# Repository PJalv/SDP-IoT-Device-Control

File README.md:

<p align="center">
    <h1 align="center">IoT Device Control System</h1>
</p>
<div align="center">
    <em>Spring 2024 Senior Design Project </em>
</div>
<p align="center">
    <em> Dylan St Laurent & Jorge Suarez </em>
</p>

<p align="center">

<p>
<p align="center">
	<!-- default option, no dependency badges. -->
</p>

<br><!-- TABLE OF CONTENTS -->

<details>
  <summary>Table of Contents</summary><br>

- [Overview](#overview)
- [Features](#features)
- [Repository Structure](#repository-structure)
- [Modules](#modules)
- [Getting Started](#getting-started)
  - [Installation](#installation)
  - [Usage](#usage)
- [Project Roadmap](#project-roadmap)
- [License](#license)
- [Acknowledgments](#acknowledgments)
</details>
<hr>

## Overview

This Senior project is structured to leverage a combination of hardware components and software technologies to provide a comprehensive IoT device control system. Here's an overview of the project's structure and the technologies used:

### Components:
1. **ESP32 Microcontrollers**: These are responsible for device control, data collection, and communication.
2. **Raspberry Pi**: Serves as a local server or gateway, facilitating the interface between ESP32 devices and the cloud server.
3. **Cloud Server**: Manages backend services, databases, and ensures data synchronization and remote access.
4. **Mobile App**: Enables users to interact with the IoT system, control devices, and view data.

### Software Technologies:
- **ESP-IDF**: This is used for programming ESP32 devices, providing essential IoT tools and libraries.
- **FreeRTOS**: Provides a real-time operating system for ESP32 devices, ensuring efficient resource management and task scheduling. We leverage FreeRTOS to separate vital ESP functions like WiFi and MQTT, allowing each to operate independently and efficiently.
- **MQTT Protocol**: Provides efficient real-time messaging across devices and servers.
- **Bun.js**: Implemented on the Raspberry Pi for fast package management and development.
- **React Native**: Utilized for developing the cross-platform mobile application.
- **WebSocket**: Supports real-time data transmission to the mobile app.
- **Go (Golang)**: Specifically used on the cloud server for its robust support for concurrency. Go routines and channels are employed to manage multiple device data streams simultaneously, significantly enhancing the system's scalability and its ability to handle large volumes of IoT device communications efficiently.

---

## Features

|     | Feature           | Description                                                                                                                                                                                         |
| --- | ----------------- | --------------------------------------------------------------------------------------------------------------------------------------------------------------------------------------------------- |
| ⚙️  | **Architecture**  | _Utilizes a modular architecture with technologies such as Go, React Native, and Expo, orchestrated by CMake for IoT device control._ |
| 🔌  | **Integrations**  | _Incorporates JWT for security, MQTT for device messaging, and WebSocket for real-time communication, supporting web and mobile functionalities._ |
| 🧩  | **Modularity**    | _Features distinct components like fan_device and main, which enhance reusability and maintainability._ |
| 🛡️  | **Security**      | _Employs JWT and secure communication protocols such as MQTT and WebSocket to ensure data protection and secure access._ |
| 🚀  | **Scalability**   | _Supports increased traffic and load efficiently through its modular architecture and scalable technologies._ |

---

## Repository Structure

```sh
└── SDP-IoT-Device-Control/
    ├── README.md
    ├── schematics
    │   ├── AudioDriver
    │   ├── Espressif
    │   ├── FanSystem
    │   ├── LED_Device
    │   └── Power
    └── source_code
        ├── IOT-App
        ├── cloud_websocket
        ├── dashboard_gui
        ├── fan_device
        ├── led_device
        └── utils
```

---

## Modules

<details closed><summary>Fan Device Main Module</summary>

| File                                                                                                                           | Summary                                                                                                                                                                                                                                                                        |
| ------------------------------------------------------------------------------------------------------------------------------ | ------------------------------------------------------------------------------------------------------------------------------------------------------------------------------------------------------------------------------------------------------------------------------ |
| [audio.h](https://github.com/PJalv/SDP-IoT-Device-Control/blob/master/source_code/fan_device/main/audio.h)                     | Enables setting up I2S audio with a defined buffer size for the fan device in the SDP-IoT-Device-Control repository.                                                                                                                                                           |
| [init.h](https://github.com/PJalv/SDP-IoT-Device-Control/blob/master/source_code/fan_device/main/init.h)                       | Initializes and finalizes the setup for the IoT fan device. Manages the initialization of FreeRTOS and GPIO, essential for device control. Part of the IoT Device Control repository structure under fan_device.                                                               |
| [main.c](https://github.com/PJalv/SDP-IoT-Device-Control/blob/master/source_code/fan_device/main/main.c)                       | Initializes system, sets up WiFi and MQTT tasks, processes events, maintains heartbeat, and handles counts. Coordinates device functionality within the SDP-IoT-Device-Control repositorys architecture.                                                                       |
| [tasks.h](https://github.com/PJalv/SDP-IoT-Device-Control/blob/master/source_code/fan_device/main/tasks.h)                     | Publishing status, playing audio, controlling breeze mode, managing tasks, establishing Wi-Fi connection, handling MQTT communication, managing heartbeats, and processing events. Crucial for fan system operation within the IoT device control architecture.                |
| [storage_nvs.h](https://github.com/PJalv/SDP-IoT-Device-Control/blob/master/source_code/fan_device/main/storage_nvs.h)         | Manages fan configuration data using Non-Volatile Storage (NVS) for the fan device within the SDP-IoT-Device-Control repositorys architecture. Key functionalities include setting and retrieving fan power, function, and duty cycle information.                             |
| [fan.h](https://github.com/PJalv/SDP-IoT-Device-Control/blob/master/source_code/fan_device/main/fan.h)                         | Implements fan control functionalities and interfaces with LED driver for RPM and power button handling. Manages duty cycle adjustments and interrupts, integrating with MQTT data for IoT device communication within the parent repositorys IoT device control architecture. |

</details>

<details closed><summary>Cloud WebSocket Broker (JavaScript)</summary>

| File                                                                                                                                     | Summary                                                                                                                                                                                                                                                                                                                                                                     |
| ---------------------------------------------------------------------------------------------------------------------------------------- | --------------------------------------------------------------------------------------------------------------------------------------------------------------------------------------------------------------------------------------------------------------------------------------------------------------------------------------------------------------------------- |
| [broker.js](https://github.com/PJalv/SDP-IoT-Device-Control/blob/master/source_code/cloud_websocket/broker-js/broker.js)                 | Establishes connectivity between MQTT broker and WebSocket server, facilitating real-time data exchange. Handles JWT token generation and verification, synchronizing data with the broker. Manages reconnections and error handling, enhancing reliability for IoT device control system.                                                                                  |

</details>

<details closed><summary>Cloud WebSocket Server (Go)</summary>

| File                                                                                                                     | Summary                                                                                                                                                                                                                                                                                               |
| ------------------------------------------------------------------------------------------------------------------------ | ----------------------------------------------------------------------------------------------------------------------------------------------------------------------------------------------------------------------------------------------------------------------------------------------------- |
| [server.go](https://github.com/PJalv/SDP-IoT-Device-Control/blob/master/source_code/cloud_websocket/server-go/server.go) | Orchestrates WebSocket communication for IoT devices. Manages client connections, token verification, and message distribution in a secure manner. Handles commands and responses, gracefully falling back on failure. Monitors domain status and switches services dynamically for robust operation. |

</details>

<details closed><summary>LED Device Managed Components (Espressif LED Strip)</summary>

| File                                                                                                                                                                      | Summary                                                                                                                                                                                                                                                    |
| ------------------------------------------------------------------------------------------------------------------------------------------------------------------------- | ---------------------------------------------------------------------------------------------------------------------------------------------------------------------------------------------------------------------------------------------------------- |
| [led_strip_spi.h](https://github.com/PJalv/SDP-IoT-Device-Control/blob/master/source_code/led_device/managed_components/espressif__led_strip/include/led_strip_spi.h)     | Implements creation of LED strip on SPI MOSI channel. Manages LED strip configuration and SPI specific settings to create LED strip handle successfully, handling errors like invalid arguments or unsupported configurations.                             |
| [led_strip.h](https://github.com/PJalv/SDP-IoT-Device-Control/blob/master/source_code/led_device/managed_components/espressif__led_strip/include/led_strip.h)             | Defines functions to manage RGB, RGBW, and HSV colors for LED strips. Contains methods to set colors for individual pixels, refresh LED memory, clear LED strip, and free resources. Enables control and customization of LED strip colors in IoT devices. |

</details>

<details closed><summary>LED Device Main Module</summary>

| File                                                                                                                           | Summary                                                                                                                                                                                                                                                                                                                                                                                                                                                                                                                                                                                                                                                                                                                                                                                                                              |
| ------------------------------------------------------------------------------------------------------------------------------ | ------------------------------------------------------------------------------------------------------------------------------------------------------------------------------------------------------------------------------------------------------------------------------------------------------------------------------------------------------------------------------------------------------------------------------------------------------------------------------------------------------------------------------------------------------------------------------------------------------------------------------------------------------------------------------------------------------------------------------------------------------------------------------------------------------------------------------------ |
| [led_config.c](https://github.com/PJalv/SDP-IoT-Device-Control/blob/master/source_code/led_device/main/led_config.c)           | Creates LED configuration for LED device with specified GPIO, LED count, and pixel format. Initializes LED strip object using SPI backend for improved performance, leveraging DMA support.                                                                                                                                                                                                                                                                                                                                                                                                                                                                                                                                                                                                                                          |
| [main.c](https://github.com/PJalv/SDP-IoT-Device-Control/blob/master/source_code/led_device/main/main.c)                       | The `main.c` file in the `led_device` module of the `SDP-IoT-Device-Control` repository serves as the main entry point for controlling LED devices. It integrates with various system components like I2S drivers, FreeRTOS tasks, LED strip libraries, MQTT protocols for communication, and Wi-Fi configurations. The code handles LED configurations, GPIO interactions, and JSON parsing to facilitate LED device functionality. Through this file, the LED device module manages LED operations, synchronization, and communication with the broader IoT infrastructure.This code supports the overarching architecture of the repository by providing a crucial component for controlling LED devices within the IoT ecosystem, ensuring seamless integration and communication with other system modules and functionalities. |
| [storage_nvs.h](https://github.com/PJalv/SDP-IoT-Device-Control/blob/master/source_code/led_device/main/storage_nvs.h)         | Manages LED device configuration data using Non-Volatile Storage in the repositorys LED device module, enhancing persistence and reliability.                                                                                                                                                                                                                                                                                                                                                                                                                                                                                                                                                                                                                                                                                        |

</details>

<details closed><summary>Dashboard GUI</summary>

| File                                                                                                                       | Summary                                                                                                                                                                                                                                                              |
| -------------------------------------------------------------------------------------------------------------------------- | -------------------------------------------------------------------------------------------------------------------------------------------------------------------------------------------------------------------------------------------------------------------- |
| [gui.py](https://github.com/PJalv/SDP-IoT-Device-Control/blob/master/source_code/dashboard_gui/gui.py)                     | Facilitates interaction with MQTT broker through Eel GUI for IoT device control. Dynamically updates broker settings, reads JSON storage, and publishes messages. Handles MQTT connection and displays connection status in the GUI, enhancing user experience.      |
| [store.py](https://github.com/PJalv/SDP-IoT-Device-Control/blob/master/source_code/dashboard_gui/store.py)                 | Manages MQTT connections, updates device statuses, and detects disconnected devices. Subscribes to specific topics, parses messages, and updates JSON storage. Handles message receiving and device disconnection checks for LED and fan devices in the IoT system.  |
| [storage.json](https://github.com/PJalv/SDP-IoT-Device-Control/blob/master/source_code/dashboard_gui/storage.json)         | Stores device status, power, and configurations for fan and LED devices-Facilitates real-time monitoring and control of devices via the dashboard GUI within the IoT system                                                                                          |

</details>

<details closed><summary>Dashboard GUI Web (JavaScript)</summary>

| File                                                                                                                    | Summary                                                                                                                                                                                                                                                                |
| ----------------------------------------------------------------------------------------------------------------------- | ---------------------------------------------------------------------------------------------------------------------------------------------------------------------------------------------------------------------------------------------------------------------- |
| [settings.js](https://github.com/PJalv/SDP-IoT-Device-Control/blob/master/source_code/dashboard_gui/web/JS/settings.js) | Retrieves, displays, and updates broker settings and status for IoT device control. Integrates with backend APIs and UI elements. Facilitates MQTT connection handling and status monitoring, ensuring seamless communication with devices.                            |
| [led.js](https://github.com/PJalv/SDP-IoT-Device-Control/blob/master/source_code/dashboard_gui/web/JS/led.js)           | Improves LED control interface. Dynamically updates LED settings and colors based on user inputs. Facilitates toggling power and selecting operation modes using MQTT messaging. Enhances user experience by enabling real-time interaction with LED device.           |
| [app.js](https://github.com/PJalv/SDP-IoT-Device-Control/blob/master/source_code/dashboard_gui/web/JS/app.js)           | Implements MQTT connection and data update logic for IoT devices integration. Manages device statuses and controls via a dashboard interface. Visualizes device status and allows dynamic device control. Dynamically updates interface elements based on device data. |
| [fan.js](https://github.com/PJalv/SDP-IoT-Device-Control/blob/master/source_code/dashboard_gui/web/JS/fan.js)           | Manages fan speed control, power toggling, and data updates using MQTT messages. Dynamically displays fan status, RPM, and mode in a responsive GUI. Enables fan mode selection and updates fan parameters through MQTT communication.                                 |

</details>

<details closed><summary>Dashboard GUI Web (HTML)</summary>

| File                                                                                                                                | Summary                                                                                                                                                                                                                                                                                                                |
| ----------------------------------------------------------------------------------------------------------------------------------- | ---------------------------------------------------------------------------------------------------------------------------------------------------------------------------------------------------------------------------------------------------------------------------------------------------------------------- |
| [index.html](https://github.com/PJalv/SDP-IoT-Device-Control/blob/master/source_code/dashboard_gui/web/html/index.html)             | Generates a responsive dashboard GUI with cards for fan and LED devices. Allows toggling power and settings, displaying device status dynamically. Incorporates Bootstrap CSS and icons for a user-friendly interface.                                                                                                 |
| [Settings.html](https://github.com/PJalv/SDP-IoT-Device-Control/blob/master/source_code/dashboard_gui/web/html/Settings.html)       | Creates a responsive settings interface for configuring the IoT devices broker connection. Features include input fields for broker name, IP address, and port number, with a Connect' button. Leverages Bootstrap for styling and jQuery for functionality.                                                           |
| [eel.js](https://github.com/PJalv/SDP-IoT-Device-Control/blob/master/source_code/dashboard_gui/web/html/eel.js)                     | Enables dynamic communication between Python and JavaScript, facilitating function exposure and asynchronous calls. Handles WebSocket interactions with an embedded Python app, supporting customization of window size and position for a web-based dashboard GUI.                                                    |
| [FanSettings.html](https://github.com/PJalv/SDP-IoT-Device-Control/blob/master/source_code/dashboard_gui/web/html/FanSettings.html) | Showcases an interactive web interface for managing fan settings. Offers power toggling, speed adjustment, breeze mode selection, and real-time statistical data display. Enhances user experience with Bootstrap styling and jQuery functionalities. Integrated for seamless device control in the SDP-IoT ecosystem. |
| [LEDSettings.html](https://github.com/PJalv/SDP-IoT-Device-Control/blob/master/source_code/dashboard_gui/web/html/LEDSettings.html) | Defines the interactive LED device settings interface in the dashboard. Displays color and function options, power toggle, and current stats visualization. Utilizes Bootstrap templates and jQuery for dynamic behavior, enhancing user control over the LED device.                                                  |

</details>

<details closed><summary>Utility Modules</summary>

| File                                                                                           | Summary                                                                                                                                                                                                                                                                       |
| ---------------------------------------------------------------------------------------------- | ----------------------------------------------------------------------------------------------------------------------------------------------------------------------------------------------------------------------------------------------------------------------------- |
| [wifi.h](https://github.com/PJalv/SDP-IoT-Device-Control/blob/master/source_code/utils/wifi.h) | Enables WiFi connectivity for IoT devices. Declares WiFi connection variables and functions. Facilitates seamless integration with parent repositorys cloud and device modules.                                                                                               |
| [mqtt.h](https://github.com/PJalv/SDP-IoT-Device-Control/blob/master/source_code/utils/mqtt.h) | Defines MQTT functionality for IoT devices, supporting integer and JSON payloads. Manages data with semaphores and tasks, handling message events through subscriptions and publications. Facilitates efficient communication within the SDP-IoT-Device-Control architecture. |

</details>

<details closed><summary>IoT App</summary>

| File                                                                                                                   | Summary                                                                                                                                                                                                                                                                                                                                                                                                                                                                                                                                                                                                  |
| ---------------------------------------------------------------------------------------------------------------------- | -------------------------------------------------------------------------------------------------------------------------------------------------------------------------------------------------------------------------------------------------------------------------------------------------------------------------------------------------------------------------------------------------------------------------------------------------------------------------------------------------------------------------------------------------------------------------------------------------------- |
| [App.js](https://github.com/PJalv/SDP-IoT-Device-Control/blob/master/source_code/IOT-App/App.js)                       | Defines navigation structure for IoT device control app using React Navigation. Screens for Home, Device List, Fan Control, and LED Control are specified with custom styling. Context from DeviceProvider wraps the app for device management.                                                                                                                                                                                                                                                                                                                                                          |

</details>
---

## Getting Started
**System Requirements:**

- **ESP32 Microcontroller**: Required for device control and data collection.
- **Linux-based Machine for Broker**: We used a Raspberry Pi with a touchscreen for this purpose.
- **Linux Machine for Cloud Server**: This could be the same machine as the broker or a separate one.
## Cloning the Repository

To get started with the SDP-IoT-Device-Control project, you need to clone the repository to your local machine. Follow the steps below:

1. **Open your terminal**: Ensure you have Git installed on your system. If not, you can download and install it from [here](https://git-scm.com/downloads).

2. **Clone the repository**: Use the following command to clone the repository to your local machine:
   ```sh
   git clone https://github.com/PJalv/SDP-IoT-Device-Control.git
   ```

3. **Navigate to the project directory**: Change your current directory to the project directory.
   ```sh
   cd SDP-IoT-Device-Control
   ```

5. **Set up environment variables**: Create a `.env` file in the root of your project and add the necessary environment variables as specified in the documentation.

### Installation

### Environment Variables

Create a `.env` file in the root of your project with the following content:
>```bash
>  BROKER_NAME='<your_broker_name>'
>  BROKER_ADDRESS='<your_broker_address>'
>  BROKER_PORT='<your_broker_port>'
>  SERVER_ADDRESS='<your_server_address>'
>  JWT_SECRET='<your_jwt_secret>'
>  OPENAI_APIKEY='<your_openai_api_key>'

### ESP32 Credential Setup
Edit the `creds-template.h` file with your network and broker credentials and save it as `credentials.h`
### Usage

### Microcontroller Setup

> Ensure you have ESP-IDF installed and configured. Use the `menuconfig` terminal of ESP-IDF to configure the `partition.csv` file.
>
> Set the COM port for your ESP32 device and then run the following commands to build, flash, and monitor the application:
>
> ```console
> $ idf.py set-target esp32
> $ idf.py menuconfig
> $ idf.py build
> $ idf.py -p [PORT] flash monitor
> ```

### Raspberry Pi Setup

> The Raspberry Pi hosts the broker, the dashboard GUI, and connects to the WebSocket server. Follow these steps to set it up:
>
> 1. Install the necessary dependencies:
>    ```console
>    $ sudo apt-get update
>    $ sudo apt-get install mosquitto mosquitto-clients
>    $ sudo apt-get install npm
>    ```
> 2. Install Bun, a fast JavaScript runtime:
>    ```console
>    $ curl -fsSL https://bun.sh/install | bash
>    ```
> 3. Clone the repository and navigate to the dashboard GUI directory:
>    ```console
>    $ git clone https://github.com/PJalv/SDP-IoT-Device-Control.git
>    $ cd SDP-IoT-Device-Control/source_code/dashboard_gui
>    ```
> 4. Install the required packages using Bun:
>    ```console
>    $ bun install
>    ```
> 5. Start the dashboard GUI:
>    ```console
>    $ bun run start
>    ```

### Server Setup

> The server is a Go application. Follow these steps to set it up:
>
> 1. Install Go from the official website: https://golang.org/dl/
> 2. Clone the repository and navigate to the server directory:
>    ```console
>    $ git clone https://github.com/PJalv/SDP-IoT-Device-Control.git
>    $ cd SDP-IoT-Device-Control/source_code/server
>    ```
> 3. Build and run the server:
>    ```console
>    $ go build server.go
>    $ ./server
>    ```

### App Setup

> The app is built using Expo. Follow these steps to set it up:
>
> 1. Install Expo CLI:
>    ```console
>    $ npm install -g expo-cli
>    ```
> 2. Clone the repository and navigate to the app directory:
>    ```console
>    $ git clone https://github.com/PJalv/SDP-IoT-Device-Control.git
>    $ cd SDP-IoT-Device-Control/source_code/IOT-App
>    ```
> 3. Install the required packages:
>    ```console
>    $ npm install
>    ```
> 4. Start the Expo development server:
>    ```console
>    $ expo start
>    ```

---

## Project Roadmap

- [x] `Refactor Fan Device`
- [ ] `Refactor LED Device`
<!-- - [ ] `` -->

---

<!-- ## Contributing

Contributions are welcome! Here are several ways you can contribute:

- **[Report Issues](https://github.com/PJalv/SDP-IoT-Device-Control/issues)**: Submit bugs found or log feature requests for the `SDP-IoT-Device-Control` project.
- **[Submit Pull Requests](https://github.com/PJalv/SDP-IoT-Device-Control/blob/main/CONTRIBUTING.md)**: Review open PRs, and submit your own PRs.
- **[Join the Discussions](https://github.com/PJalv/SDP-IoT-Device-Control/discussions)**: Share your insights, provide feedback, or ask questions.

<details closed>
<summary>Contributing Guidelines</summary>

1. **Fork the Repository**: Start by forking the project repository to your github account.
2. **Clone Locally**: Clone the forked repository to your local machine using a git client.
   ```sh
   git clone https://github.com/PJalv/SDP-IoT-Device-Control
   ```
3. **Create a New Branch**: Always work on a new branch, giving it a descriptive name.
   ```sh
   git checkout -b new-feature-x
   ```
4. **Make Your Changes**: Develop and test your changes locally.
5. **Commit Your Changes**: Commit with a clear message describing your updates.
   ```sh
   git commit -m 'Implemented new feature x.'
   ```
6. **Push to github**: Push the changes to your forked repository.
   ```sh
   git push origin new-feature-x
   ```
7. **Submit a Pull Request**: Create a PR against the original project repository. Clearly describe the changes and their motivations.
8. **Review**: Once your PR is reviewed and approved, it will be merged into the main branch. Congratulations on your contribution!
</details>

<details closed> -->
<summary>Contributor Graph</summary>
<br>
<p align="center">
   
</p>
</details>

---

## License

This project is protected under the [MIT](https://choosealicense.com/licenses/mit/) License.

---

## Acknowledgments

- **Advisor: Professor Tim Lin**
  - Electrical and Computer Engineering Department, College of Engineering
  - hlin@cpp.edu

[**Return**](#overview)

---

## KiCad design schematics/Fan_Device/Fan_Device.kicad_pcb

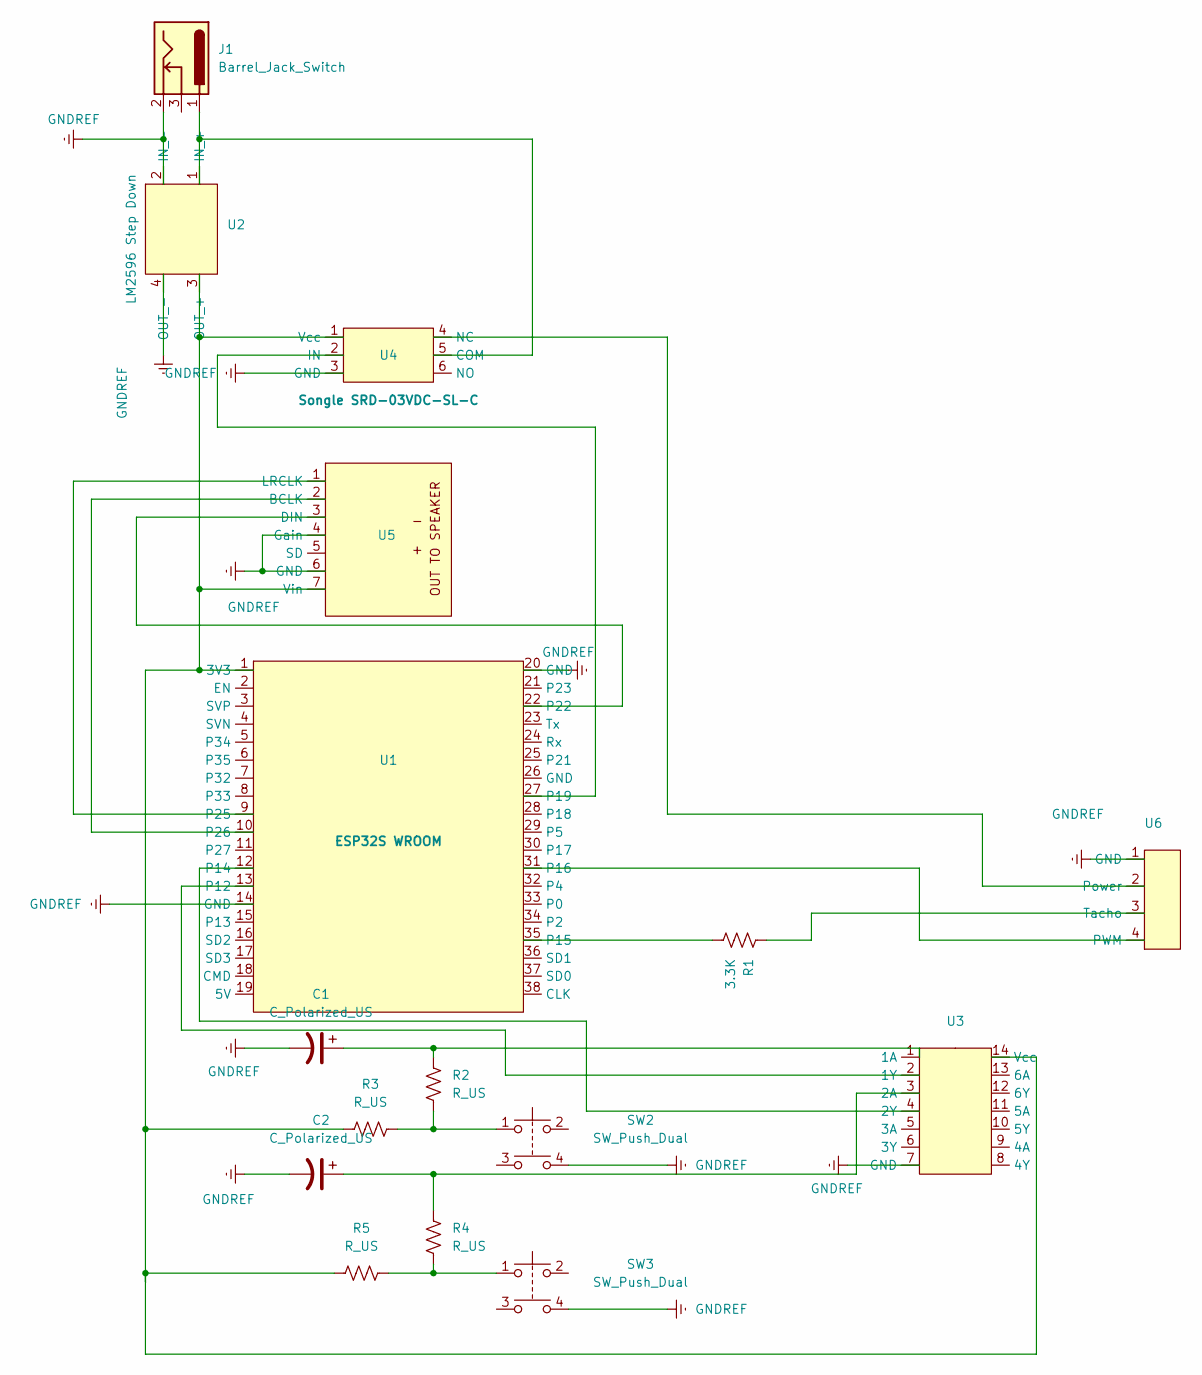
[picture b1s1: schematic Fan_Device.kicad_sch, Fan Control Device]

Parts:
C1, C2: C_Polarized_US; CP_Radial_D5.0mm_P2.50mm
J1: Barrel_Jack_Switch; BarrelJack_Kycon_KLDX-0202-xC_Horizontal (BreadBoard)
R1: 3.3K; R_Axial_DIN0309_L9.0mm_D3.2mm_P15.24mm_Horizontal
R2, R3, R4, R5: R_US; R_Axial_DIN0309_L9.0mm_D3.2mm_P15.24mm_Horizontal
SW2, SW3: SW_Push_Dual; SW_PUSH_6mm_H5mm
U1: ESP32S WROOM; ESP-WROOM-32
U2: LM2596 Step Down
U3: DIP-SN74HC14N
U4: Songle SRD-03VDC-SL-C; Songle Relay Module
U5: MAX98357A Board
U6: PinHeader_1x04_P2.54mm_Vertical

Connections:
GNDREF: C1.2, C2.2, J1.2, SW2.4, SW3.4, U1.14 (GND), U1.20 (GND), U2.2 (IN_-), U2.4 (OUT_-), U3.7 (GND), U4.3 (GND), U5.4 (Gain), U5.6 (GND), U6.1 (GND)
unnamed: R2.2, R3.1, SW2.1
unnamed: R4.2, R5.1, SW3.1
unnamed: R3.2, R5.2, U1.1 (3V3), U2.3 (OUT_+), U3.14 (Vcc), U4.1 (Vcc), U5.7 (Vin)
unnamed: U1.13 (P12), U3.2 (1Y)
unnamed: U1.12 (P14), U3.4 (2Y)
unnamed: R1.2, U1.35 (P15)
unnamed: U1.31 (P16), U6.4 (PWM)
unnamed: U1.27 (P19), U4.2 (IN)
unnamed: U1.22, U5.3 (DIN)
unnamed: U1.9 (P25), U5.1 (LRCLK)
unnamed: U1.10 (P26), U5.2 (BCLK)
unnamed: J1.1, U2.1 (IN_+), U4.5 (COM)
unnamed: C1.1, R2.1, U3.1 (1A)
unnamed: C2.1, R4.1, U3.3 (2A)
unnamed: U4.4 (NC), U6.2 (Power)
unnamed: R1.1, U6.3 (Tacho)

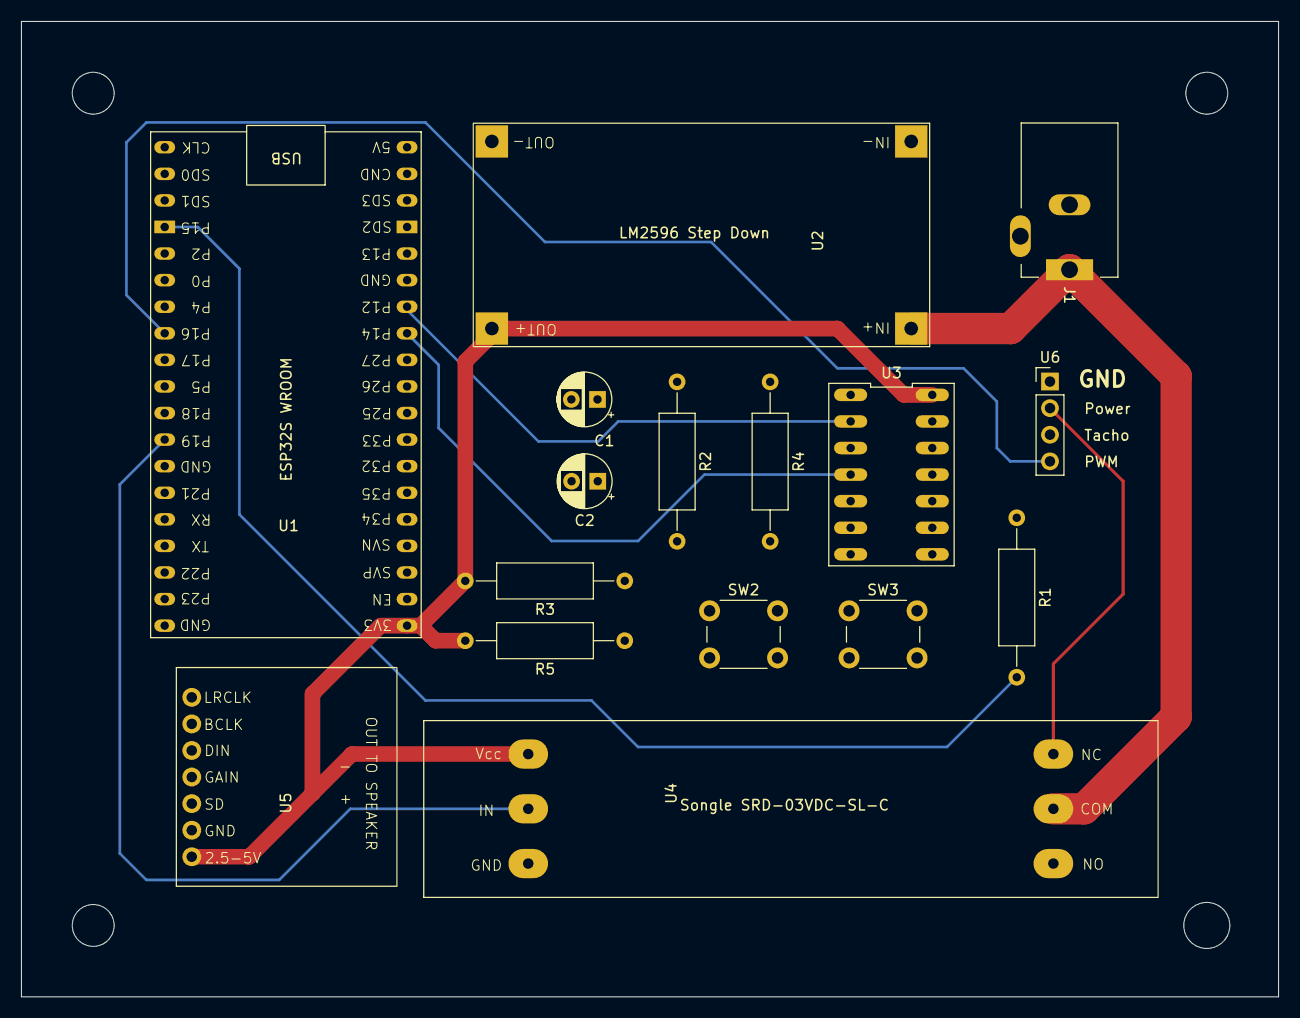
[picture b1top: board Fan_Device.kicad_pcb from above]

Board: 4 copper layers, 120.1 x 93.2 mm, 16 parts (0 on the bottom side), 17 nets.

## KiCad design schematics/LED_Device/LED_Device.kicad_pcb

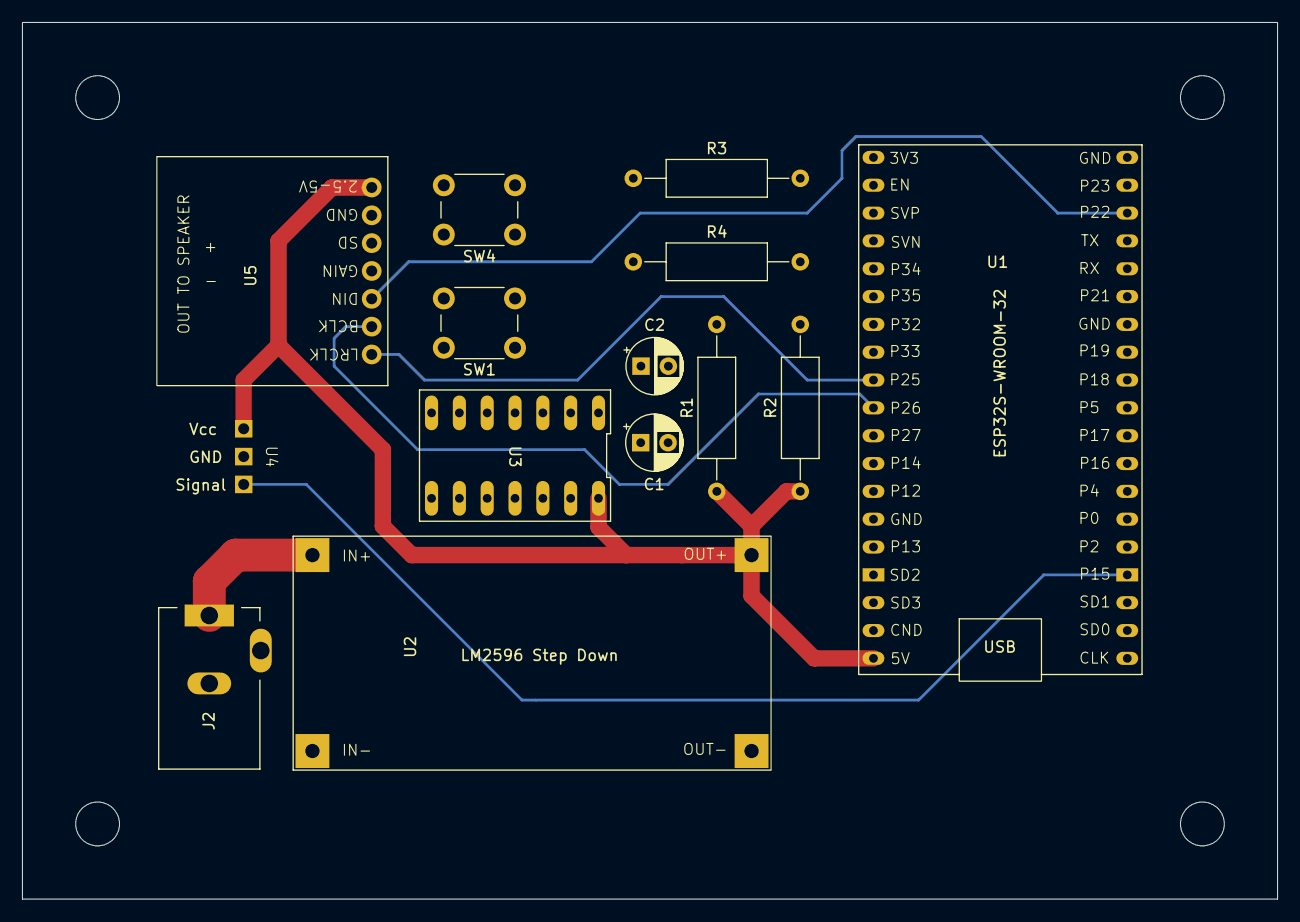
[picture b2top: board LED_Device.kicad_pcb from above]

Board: 4 copper layers, 114.6 x 80.0 mm, 14 parts (0 on the bottom side), 13 nets.

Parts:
C1, C2: 1uF; CP_Radial_D5.0mm_P2.50mm
J2: Barrel_Jack_Switch; BarrelJack_Kycon_KLDX-0202-xC_Horizontal (BreadBoard)
R1, R2: 15k; R_Axial_DIN0309_L9.0mm_D3.2mm_P15.24mm_Horizontal
R3, R4: 1k; R_Axial_DIN0309_L9.0mm_D3.2mm_P15.24mm_Horizontal
SW1, SW4: SW_Push_Dual; SW_PUSH_6mm_H5mm
U1: ESP32S-WROOM-32; ESP-WROOM-32
U2: LM2596 Step Down
U3: DIP-SN74HC14N
U4: MountingRail3x1
U5: MAX98357A Board

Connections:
GNDREF: C1.2, C2.2, J2.2, SW1.4, SW4.4, U1.14 (GND), U1.20 (GND), U2.2 (IN_-), U2.4 (OUT_-), U3.7 (GND), U4.2 (GND), U5.4 (Gain), U5.6 (GND)
unnamed: R1.2, R4.1, SW1.1
unnamed: R2.2, R3.1, SW4.1
unnamed: R1.1, R2.1, U1.19 (5V), U2.3 (OUT_+), U3.14 (Vcc), U4.1 (5V), U5.7 (Vin)
unnamed: U1.13 (P12), U3.2 (1Y)
unnamed: U1.12 (P14), U3.4 (2Y)
unnamed: U1.35 (P15), U4.3 (Signal)
unnamed: U1.22, U5.3 (DIN)
unnamed: U1.9 (P25), U5.1 (LRCLK)
unnamed: U1.10 (P26), U5.2 (BCLK)
unnamed: J2.1, U2.1 (IN_+)
unnamed: C1.1, R3.2, U3.1 (1A)
unnamed: C2.1, R4.2, U3.3 (2A)

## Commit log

2023-12-19 Hello
2023-12-19 Hello from pc
2023-12-19 Added first speaker schematic.
2023-12-19 Change main.c
2023-12-19 Testing vTaskDelay in fan_device
2023-12-19 Added wifi.c file, with CMakeLists.txt edit for it
2023-12-19 Move wifi.c to utils for common inclusion.
2023-12-20 Update credentials_template.h for Broker URL
2023-12-20 Add mqtt.c Update main.c for MQTT testing
2023-12-21 Addition of Schematics & Libraries
    Added created libraries for espressif and audio driver symbology.
2023-12-21 Test MQTT Task Delay.
2023-12-21 Update mqtt delay
2023-12-21 tweach mqtt delay
2023-12-23 Update main.c for First Fan Test
2023-12-23 tweak main.c
2023-12-23 Add tachometer test
2023-12-23 Tach Test
2023-12-23 First Official Test for Fan integration
2024-01-02 Add component for LED device control
2024-01-03 Update Fan Device
2024-01-03 mqtt library is not common util
2024-01-03 Create storage_nvs library
2024-01-03 update storage_nvs
2024-01-03 update LED device for control
2024-01-03 update led device
2024-01-03 update gitignore
2024-01-03 Update MQTT and Fan Device for new communication format
2024-01-04 update Fan Device and mqtt library
2024-01-04 Update LED device for mqtt color change
2024-01-09 Add button support for fan device
2024-01-09 Update LES device
2024-01-11 Update LED device with button support.
2024-01-12 create dashboard gui folder
2024-01-12 create store.py for data updating
2024-01-17 Updated Schematic Drawings
    Schematics have been updated to the current build status of the project.
2024-01-20 Update HTML for Dashboard and Fan Settings
    added dashboard HTML for Rasberry Pi operating screen. Work started on Fan Settings page
2024-01-20 HUGE UPDATE to LED Device: change from RMT to SPI backend refactor status publishing, add rainbow effect function, add function storage.
2024-01-20 Update LED DEvice,rainbow function, spi backend, function storage)
2024-01-20 update dashboard backend
2024-01-20 update gui dashboard
2024-01-24 Update to GUI including LED Settings page and settings
2024-01-25 reorganize file structure; refactor webpage styles
2024-01-30 Create led.js MQTT connection logic is now controlled from JS code (app.js) Tweak LED Settings for color retrieval
2024-01-31 Update LED device: add heartbeat
2024-01-31 Update Dashboard GUI: LED function control
2024-02-03 Visual update to index and main settings page
2024-03-11 Update Dashboard GUI files
2024-03-11 GUI HTML Update
2024-03-11 Update Dashboard Gui
2024-03-17 Update FAN device: - add breeze mode - add audio playback response
2024-03-17 Update Fan storage
2024-03-17 Revert files from previous commit
2024-03-23 MASSIVE REFACTOR OF FAN DEVICE
2024-03-23 Update Utils directory
2024-03-29 Included mobile application GUI screens & navigation
2024-03-29 Undo
2024-03-29 Included mobile app GUI screens & navigation
2024-04-08 **EDIT .env PATHS** Add cloud websocket directory (contains server program & broker ws program) Update App: Add WS support and initial frontend update
2024-04-09 Add Dockerfile for broker image General broker improvements
2024-04-19 Update server: Service status polling
2024-04-21 Update Client and Server for ssl certificate authority
2024-04-22 MASSIVE REFACTOR: Fix WebSocket Error Handling move each page to to its own file(home, device, etc) Add Fan Page Add Led Page
2024-04-25 Update IoT App
2024-04-26 Remove Speaker Schematics
2024-05-22 Reorganization of Hardware Files
    Reorganized hardware schematics, symbols, and footprints for easy navigation

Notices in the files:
README.md:
License:
This project is protected under the [MIT](https://choosealicense.com/licenses/mit/) License.
